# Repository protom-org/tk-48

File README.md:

# tk-48

- 8048を使ったトレーニングボード。シリアル通信でHEXファイルをボード上のRAM又はEEPROMにアップロードして実行が可能。
- KiCADで設計PCBWayで白レジスト基板を作成。

## [サポートサイトのWebページ](https://www.protom.org/micon/tk-48)

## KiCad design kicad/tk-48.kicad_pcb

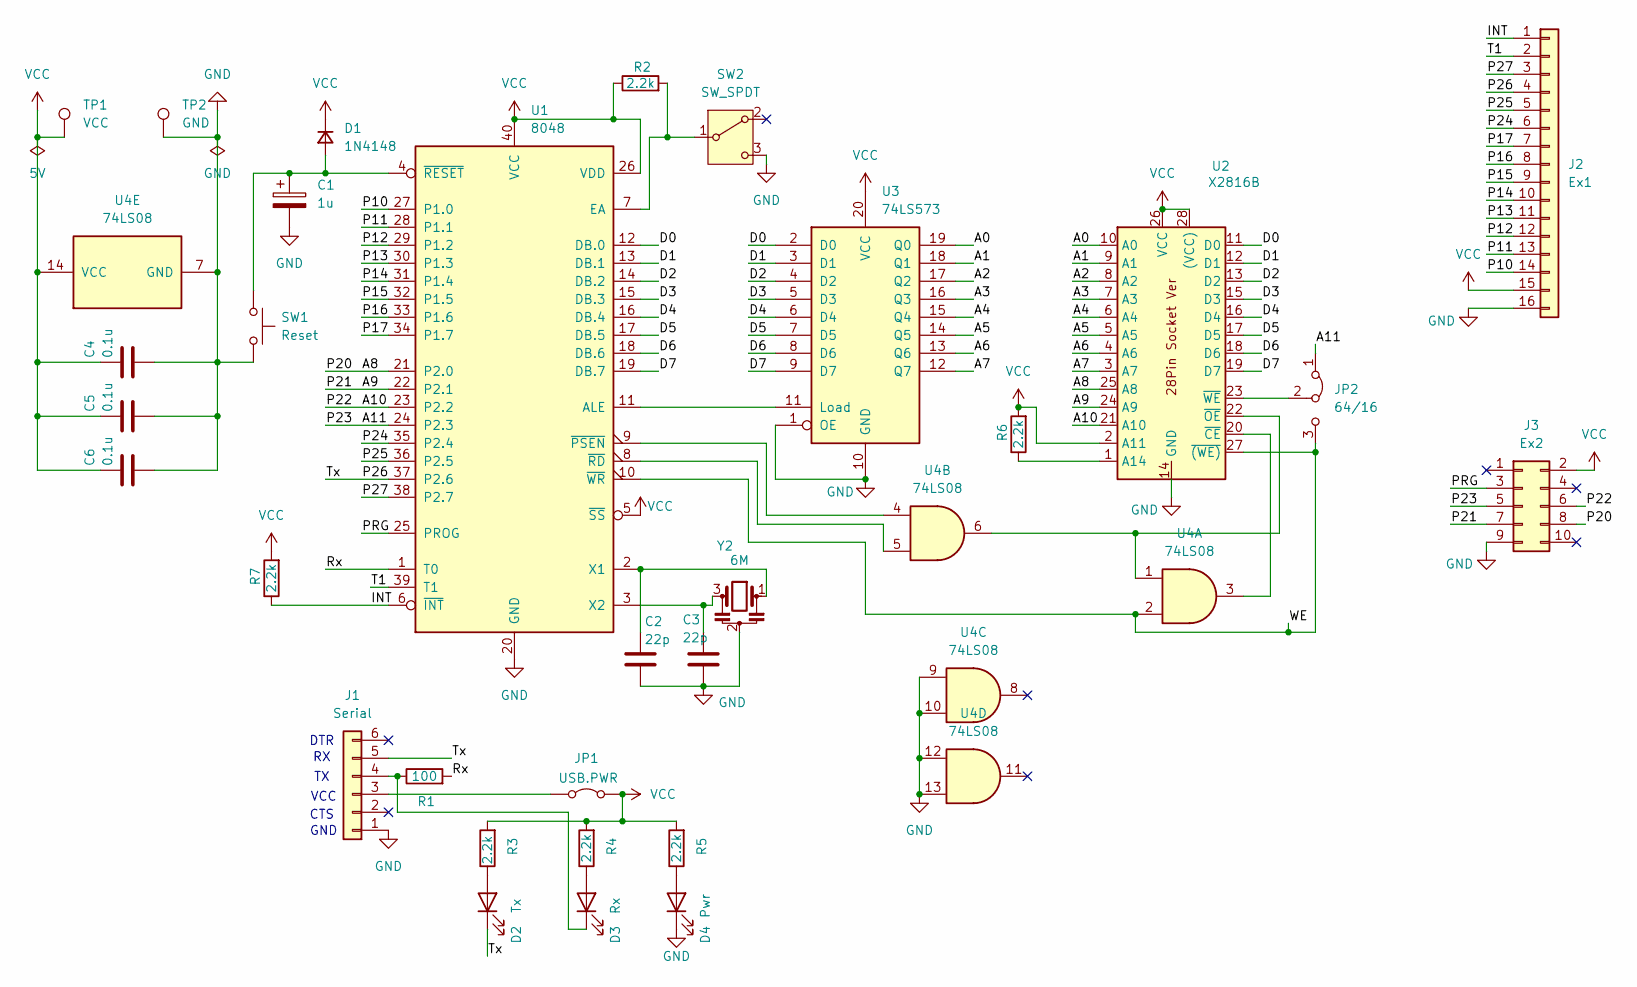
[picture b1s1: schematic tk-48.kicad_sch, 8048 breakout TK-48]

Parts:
C1: 1u; CP_Radial_D4.0mm_P1.50mm
C2, C3: 22p; C_Disc_D3.0mm_W1.6mm_P2.50mm
C4, C5, C6: 0.1u; C_Disc_D3.8mm_W2.6mm_P2.50mm
D1: 1N4148; D_DO-34_SOD68_P7.62mm_Horizontal
D2: Tx; LED_D3.0mm
D3: Rx; LED_D3.0mm
D4: Pwr; LED_D3.0mm
J1: Serial; PinHeader_1x06_P2.54mm_Horizontal
J2: Ex1; PinSocket_1x16_P2.54mm_Vertical
J3: Ex2; PinHeader_2x05_P2.54mm_Vertical
JP1: USB.PWR; PinHeader_1x02_P2.54mm_Vertical
JP2: 64/16; PinHeader_1x03_P2.54mm_Vertical
R1: 100; R_Axial_DIN0204_L3.6mm_D1.6mm_P7.62mm_Horizontal
R2, R3, R4, R5, R6, R7: 2.2k; R_Axial_DIN0204_L3.6mm_D1.6mm_P7.62mm_Horizontal
SW1: Reset; SW_PUSH_6mm_H8.5mm
SW2: SW_SPDT; SW_Slide-03_Wuerth-WS-SLTV_10x2.5x6.4_P2.54mm
TP1: VCC; TestPoint_Loop_D1.80mm_Drill1.0mm_Beaded
TP2: GND; TestPoint_Loop_D1.80mm_Drill1.0mm_Beaded
U1: 8048; DIP-40_W15.24mm_Socket
U2: X2816B; DIP-28_W15.24mm_Socket
U3: 74LS573; DIP-20_W7.62mm_Socket
U4: 74LS08; DIP-14_W7.62mm_Socket
Y2: 6M; Resonator_Murata_CSTLSxxxX-3Pin_W5.5mm_H3.0mm

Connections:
/A0: U2.10 (A0), U3.19 (Q0)
/A1: U2.9 (A1), U3.18 (Q1)
/A2: U2.8 (A2), U3.17 (Q2)
/A3: U2.7 (A3), U3.16 (Q3)
/A4: U2.6 (A4), U3.15 (Q4)
/A5: U2.5 (A5), U3.14 (Q5)
/A6: U2.4 (A6), U3.13 (Q6)
/A7: U2.3 (A7), U3.12 (Q7)
/A8: J3.8, U1.21 (P2.0), U2.25 (A8)
/A9: J3.7, U1.22 (P2.1), U2.24 (A9)
/A10: J3.6, U1.23 (P2.2), U2.21 (A10)
/A11: J3.5, JP2.1 (A), U1.24 (P2.3)
/D0: U1.12 (DB.0), U2.11 (D0), U3.2 (D0)
/D1: U1.13 (DB.1), U2.12 (D1), U3.3 (D1)
/D2: U1.14 (DB.2), U2.13 (D2), U3.4 (D2)
/D3: U1.15 (DB.3), U2.15 (D3), U3.5 (D3)
/D4: U1.16 (DB.4), U2.16 (D4), U3.6 (D4)
/D5: U1.17 (DB.5), U2.17 (D5), U3.7 (D5)
/D6: U1.18 (DB.6), U2.18 (D6), U3.8 (D6)
/D7: U1.19 (DB.7), U2.19 (D7), U3.9 (D7)
/INT: J2.1, R7.1, U1.6 (~INT)
/P10: J2.14, U1.27 (P1.0)
/P11: J2.13, U1.28 (P1.1)
/P12: J2.12, U1.29 (P1.2)
/P13: J2.11, U1.30 (P1.3)
/P14: J2.10, U1.31 (P1.4)
/P15: J2.9, U1.32 (P1.5)
/P16: J2.8, U1.33 (P1.6)
/P17: J2.7, U1.34 (P1.7)
/P24: J2.6, U1.35 (P2.4)
/P25: J2.5, U1.36 (P2.5)
/P26: D2.1 (K), J1.5, J2.4, U1.37 (P2.6)
/P27: J2.3, U1.38 (P2.7)
/PRG: J3.3, U1.25 (PROG)
/Rx: R1.2, U1.1 (T0)
/T1: J2.2, U1.39 (T1)
/WE: JP2.3 (B), U1.10 (~WR), U2.27 (~(WE)), U4.2
GND: C1.2, C2.2, C3.2, C4.2, C5.2, C6.2, D4.1 (K), J1.1, J2.16, J3.9, SW1.2, SW2.3 (C), TP2.1, U1.20 (GND), U2.14 (GND), U3.1 (OE), U3.10 (GND), U4.7 (GND), U4.9, U4.10, U4.12, U4.13, Y2.2
unnamed: C1.1, D1.2 (A), SW1.1, U1.4 (~RESET)
unnamed: D2.2 (A), R3.1
unnamed: D3.2 (A), R4.1
unnamed: D3.1 (K), J1.4, R1.1
unnamed: D4.2 (A), R5.1
unnamed: J1.3, JP1.1 (A)
unnamed: JP2.2 (C), U2.23 (~WE)
unnamed: R2.2, SW2.1 (B), U1.7 (EA)
unnamed: U1.11 (ALE), U3.11 (Load)
unnamed: C2.1, U1.2 (X1), Y2.1
unnamed: C3.1, U1.3 (X2), Y2.3
unnamed: U1.9 (~PSEN), U4.4
unnamed: U1.8 (~RD), U4.5
unnamed: R6.1, U2.1 (A14)
unnamed: U2.20 (~CE), U4.3
unnamed: U2.22 (~OE), U4.1, U4.6
VCC: C4.1, C5.1, C6.1, D1.1 (K), J2.15, J3.2, JP1.2 (B), R2.1, R3.2, R4.2, R5.2, R6.2, R7.2, TP1.1, U1.5 (~SS), U1.26 (VDD), U1.40 (VCC), U2.2 (A11), U2.26 (VCC), U2.28 ((VCC)), U3.20 (VCC), U4.14 (VCC)

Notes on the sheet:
CTS
VCC
DTR
GND

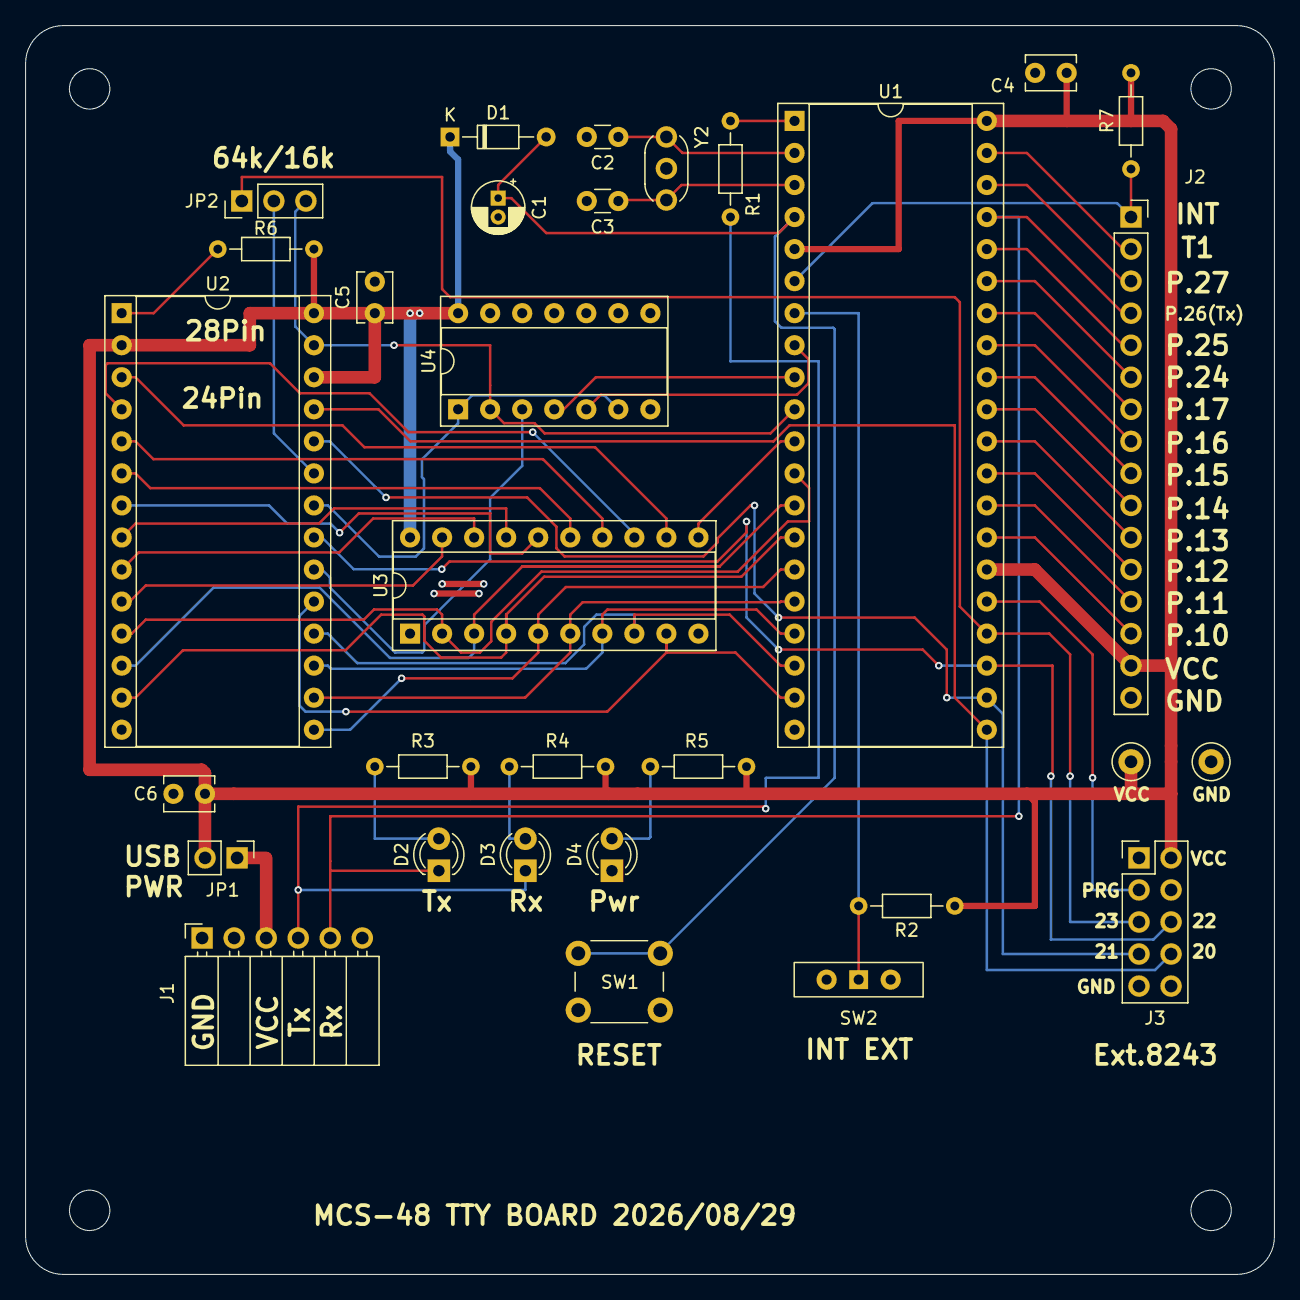
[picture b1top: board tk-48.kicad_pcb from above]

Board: 2 copper layers, 99.0 x 99.0 mm, 35 parts (0 on the bottom side), 55 nets.

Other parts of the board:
REF1, REF2, REF3, REF4: MountingHole_3.2mm_M3

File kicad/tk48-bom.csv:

Designator,Quantity,Value,Footprint
C1,1,1u セラミック,CP_Radial_D4.0mm_P1.50mm
"C2, C3",2,22p セラミック,C_Disc_D3.0mm_W1.6mm_P2.50mm
"C4, C5, C6",3,0.1u セラミック,C_Disc_D3.8mm_W2.6mm_P2.50mm
D1,1,1SS131,D_DO-34_SOD68_P7.62mm_Horizontal
D2,1,Pure Green 3mm LED,LED_D3.0mm
D3,1,Pure Green 3mm LED,LED_D3.0mm
D4,1,Yellow 3mm LED,LED_D3.0mm
J1,1,1x6 L Pin Header,PinHeader_1x06_P2.54mm_Horizontal
J2,1,1x16 Pin Socket,PinSocket_1x16_P2.54mm_Vertical
J3,1,2x5 Pin Header,PinHeader_2x05_P2.54mm_Vertical
JP1,1,1x2 Pin Header,PinHeader_1x02_P2.54mm_Vertical
JP2,1,1x3 Pin Header,PinHeader_1x03_P2.54mm_Vertical
R1,1,100 1/6W,R_Axial_DIN0204_L3.6mm_D1.6mm_P7.62mm_Horizontal
"R2, R3, R4, R5, R6, R7",6,2.2k 1/6W,R_Axial_DIN0204_L3.6mm_D1.6mm_P7.62mm_Horizontal
SW1,1,6mm タクトSW,SW_PUSH_6mm_H8.5mm
SW2,1,スライドSW 3P,SW_Slide-03_Wuerth-WS-SLTV_10x2.5x6.4_P2.54mm
TP1,1,,TestPoint_Loop_D1.80mm_Drill1.0mm_Beaded
TP2,1,,TestPoint_Loop_D1.80mm_Drill1.0mm_Beaded
U1,1,uPD8748,DIP-40_W15.24mm_Socket
U2,1,6116 6264 62256 ...,DIP-28_W15.24mm_Socket
U3,1,74LS573,DIP-20_W7.62mm_Socket
U4,1,74LS08,DIP-14_W7.62mm_Socket
Y2,1,Xtal 6MHz,Resonator_Murata_CSTLSxxxX-3Pin_W5.5mm_H3.0mm
